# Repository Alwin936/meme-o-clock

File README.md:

This is the Meme-O-Clock PCB.

I built it with the help of a Youtube tutorial, ChatGPT, and KiCAD.

This is my first ever time designing a PCB.

I chose an Arduino Nano ESP 32 as my microcontroller due to the familiar ecosystem and WiFi capabilities.

The arduino will instruct a speaker and display to work as an alarm clock, with custom sounds and objects displayed to wake you up in a personal way.

Light sensor automatically adjusts display brightness based on the room.

Motion sensor will turn on display when motion detected.

MAX98357A amplifier for 5W, 8Ohm Speaker.

The whole project should cost under $30.

## Bill of Materials (BOM)

All prices are in USD and exclude shipping and tax. Prices are estimates or listed prices and may change.

### 1. PCB Components

| Component | Qty. | Part / Model | Unit Price | Supplier |
|---|---:|---|---:|---|
| Arduino Nano ESP32 | 1 | Arduino Nano ESP32 | $19.30 | [Arduino](https://store-usa.arduino.cc/products/nano-esp32) |
| USB-C receptacle | 1 | GCT USB4105-GF-A | $0.80 | [DigiKey](https://www.digikey.com/en/products/detail/gct/USB4105-GF-A/11198441) |
| JST EH 4-pin connector | 1 | S4B-EH | $0.116 | [GAM-GEC](https://gam-gec.com/product/s4b-eh/) |
| JST EH 2-pin connector | 1 | S2B-EH | $0.14 | [GAM-GEC](https://gam-gec.com/product/s2b-eh/) |
| JST EH 3-pin connector | 1 | S3B-EH | $0.17 | [GAM-GEC](https://gam-gec.com/product/s3b-eh/) |
| 10 kΩ resistor, 0603 | 4 | Stackpole RMCF0603FG10K0 | $0.10 | [DigiKey](https://www.digikey.com/en/products/detail/stackpole-electronics-inc/RMCF0603FG10K0/1761236) |
| 5.1 kΩ resistor, 0603 | 2 | Stackpole RNCF0603DTE5K10 | $0.10 | [DigiKey](https://www.digikey.com/en/products/detail/stackpole-electronics-inc/RNCF0603DTE5K10/6264054) |
| 634 kΩ resistor, 0603 | 1 | Vishay CRCW0603634KFKEA | $0.10 | [DigiKey](https://www.digikey.com/en/products/detail/vishay-dale/CRCW0603634KFKEA/1180130) |
| 6 × 6 mm tactile pushbutton, THT | 4 | Schurter 1301.9317 | $0.373 | [Newark](https://www.newark.com/) |
| I²S audio amplifier | 1 | MAX98357AETE+T | $4.08 | [DigiKey](https://www.digikey.com/en/products/detail/analog-devices-inc-maxim-integrated/MAX98357AETE-T/4936122) |
| Ambient light sensor | 1 | APDS-9306 | TBD | [Broadcom Datasheet](https://docs.broadcom.com/docs/AV02-4755EN) |
| Ceramic capacitor | 5 | 100 nF, 0603 | $0.05 | [TME](https://www.tme.com/us/en-us/details/c0603c104k4rac7081/mlcc-smd-capacitors/kemet/) |
| Ceramic capacitor | 1 | 1 µF, 0603 | $0.13 | [Mouser](https://www.mouser.com/en/c/passive-components/capacitors/ceramic-capacitors/mlccs-multilayer-ceramic-capacitors/multilayer-ceramic-capacitors-mlcc-smd-smt/?capacitance=1+uF&case+code+-+in=0603&dielectric=X7R&termination=Standard&voltage+rating+dc=10+VDC) |
| Ceramic capacitor | 1 | 10 µF, 0603 | $0.06 | [Mylsco](https://spartce.com/products/c1608x5r1a106m080ac-1) |

### 2. External Components

| Component | Qty. Needed | Product | Pack Price | Effective Unit Price | Supplier |
|---|---:|---|---:|---:|---|
| Speaker, 28 mm, 8 Ω, 2 W | 1 | 6-piece pack | TBD | TBD | [Amazon](https://www.amazon.com/dp/B09YGDQV3Z) |
| OLED display, 0.96 in, 128 × 64, SSD1306, I²C | 1 | ELEGOO 3-piece pack | $9.99 | $3.33 | [Amazon](https://www.amazon.com/dp/B0D2RMQQHR) |

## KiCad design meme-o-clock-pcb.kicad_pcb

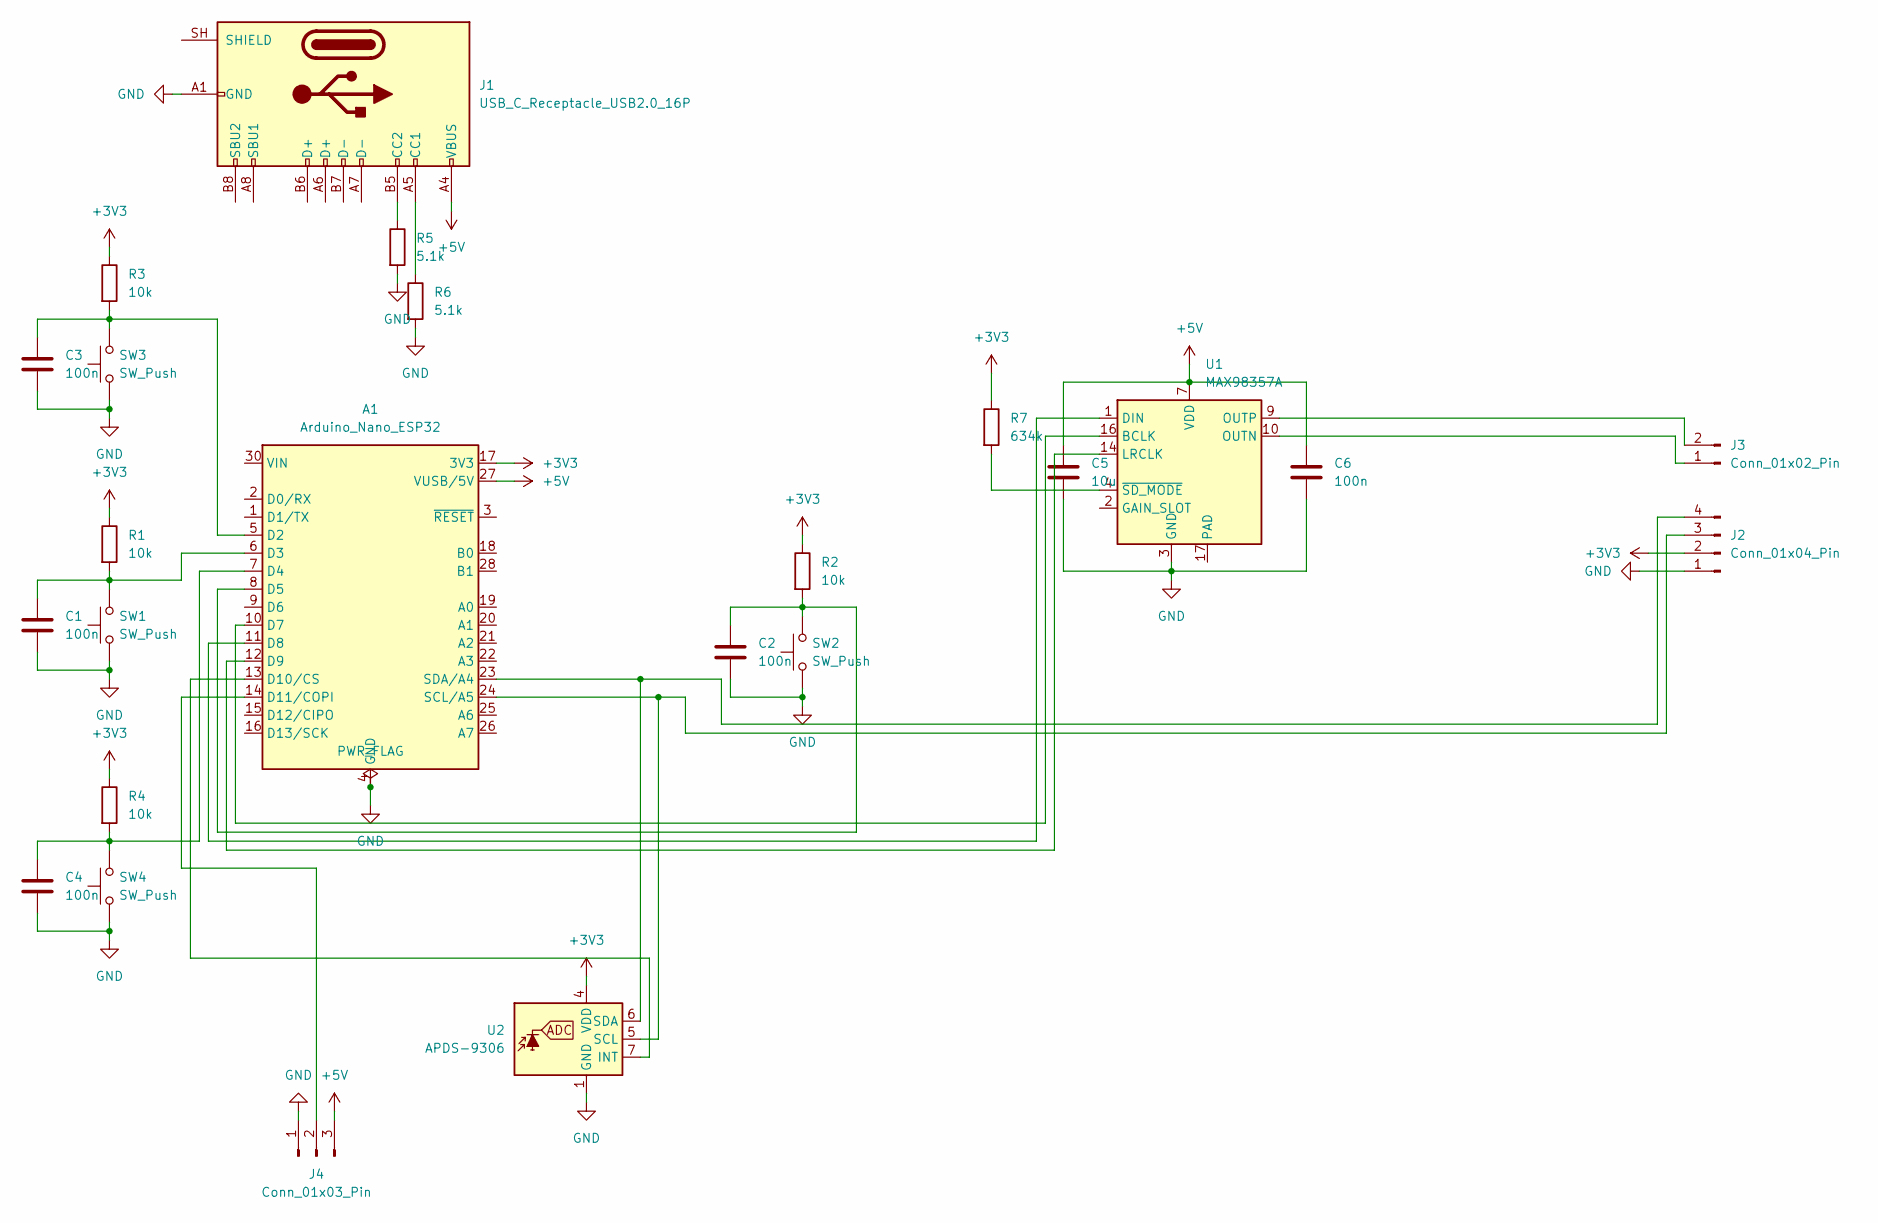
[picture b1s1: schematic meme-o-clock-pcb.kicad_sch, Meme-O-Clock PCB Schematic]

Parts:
A1: Arduino_Nano_ESP32; Arduino_Nano
C1, C2, C3, C4, C6: 100n; C_0603_1608Metric
C5: 10u; C_0805_2012Metric
J1: USB_C_Receptacle_USB2.0_16P; USB_C_Receptacle_GCT_USB4105-xx-A_16P_TopMnt_Horizontal
J2: Conn_01x04_Pin; PinHeader_1x04_P2.54mm_Vertical_SMD_Pin1Left
J3: Conn_01x02_Pin; JST_PH_B2B-PH-K_1x02_P2.00mm_Vertical
J4: Conn_01x03_Pin; PinHeader_1x03_P2.54mm_Vertical
R1, R2, R3, R4: 10k; R_0603_1608Metric
R5, R6: 5.1k; R_0603_1608Metric
R7: 634k; R_0603_1608Metric
SW1, SW2, SW3, SW4: SW_Push; SW_PUSH_6mm
U1: MAX98357A; TQFN-16-1EP_3x3mm_P0.5mm_EP1.23x1.23mm
U2: APDS-9306; Broadcom_LGA-8_2x2mm_P0.53mm

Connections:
+3V3: A1.17 (3V3), J2.2, R1.1, R2.1, R3.1, R4.1, R7.1, U2.4 (VDD)
+5V: A1.27 (VUSB/5V), C5.1, C6.1, J1.A4 (VBUS), J1.A9 (VBUS), J1.B4 (VBUS), J1.B9 (VBUS), J4.3, U1.7 (VDD), U1.8 (VDD)
GND: A1.4 (GND), A1.29 (GND), C1.2, C2.2, C3.2, C4.2, C5.2, C6.2, J1.A1 (GND), J1.A12 (GND), J1.B1 (GND), J1.B12 (GND), J2.1, J4.1, R5.2, R6.2, SW1.1, SW2.1, SW3.1, SW4.1, U1.3 (GND), U1.11 (GND), U1.15 (GND), U2.1 (GND)
unnamed: A1.5 (D2), C3.1, R3.2, SW3.2
unnamed: A1.6 (D3), C1.1, R1.2, SW1.2
unnamed: A1.7 (D4), C4.1, R4.2, SW4.2
unnamed: A1.8 (D5), C2.1, R2.2, SW2.2
unnamed: A1.10 (D7), U1.16 (BCLK)
unnamed: A1.11 (D8), U1.1 (DIN)
unnamed: A1.12 (D9), U1.14 (LRCLK)
unnamed: A1.13 (D10/CS), U2.7 (INT)
unnamed: A1.14 (D11/COPI), J4.2
unnamed: A1.24 (SCL/A5), J2.3, U2.5 (SCL)
unnamed: A1.23 (SDA/A4), J2.4, U2.6 (SDA)
unnamed: J1.A5 (CC1), R6.1
unnamed: J1.B5 (CC2), R5.1
unnamed: J3.1, U1.10 (OUTN)
unnamed: J3.2, U1.9 (OUTP)
unnamed: R7.2, U1.4 (~SD_MODE)

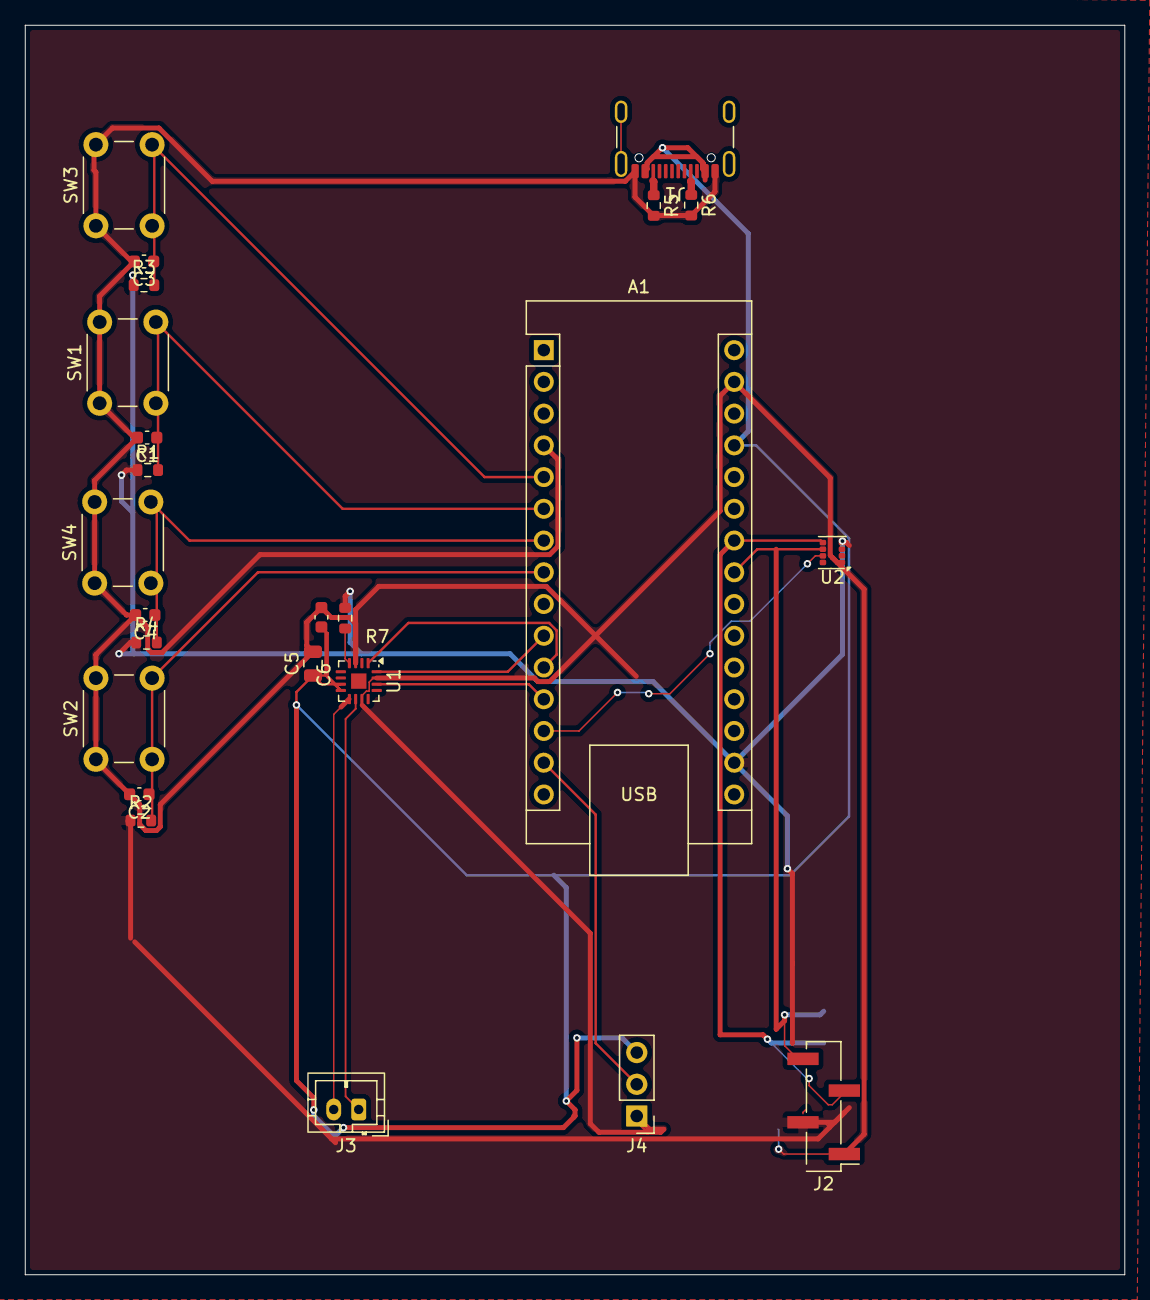
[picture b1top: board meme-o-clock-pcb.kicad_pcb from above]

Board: 4 copper layers, 88.0 x 100.0 mm, 24 parts (0 on the bottom side), 19 nets.

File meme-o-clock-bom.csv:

"Reference","Qty","Value","DNP","Exclude from BOM","Exclude from Board","Exclude from Simulation","Exclude from Position Files","Footprint","Datasheet"
"A1","1","Arduino_Nano_ESP32","","","","","${EXCLUDE_FROM_POS_FILES}","Module:Arduino_Nano","https://docs.arduino.cc/resources/datasheets/ABX00083-datasheet.pdf"
"C1,C2,C3,C4,C6","5","100n","","","","","${EXCLUDE_FROM_POS_FILES}","Capacitor_SMD:C_0603_1608Metric",""
"C5","1","10u","","","","","${EXCLUDE_FROM_POS_FILES}","Capacitor_SMD:C_0805_2012Metric",""
"J1","1","USB_C_Receptacle_USB2.0_16P","","","","","${EXCLUDE_FROM_POS_FILES}","Connector_USB:USB_C_Receptacle_GCT_USB4105-xx-A_16P_TopMnt_Horizontal","https://www.usb.org/sites/default/files/documents/usb_type-c.zip"
"J2","1","Conn_01x04_Pin","","","","","${EXCLUDE_FROM_POS_FILES}","Connector_JST:JST_EH_S4B-EH_1x04_P2.50mm_Horizontal",""
"J3","1","Conn_01x02_Pin","","","","","${EXCLUDE_FROM_POS_FILES}","Connector_JST:JST_EH_S2B-EH_1x02_P2.50mm_Horizontal",""
"J4","1","Conn_01x03_Pin","","","","","${EXCLUDE_FROM_POS_FILES}","Connector_JST:JST_EH_S3B-EH_1x03_P2.50mm_Horizontal",""
"R1,R2,R3,R4","4","10k","","","","","${EXCLUDE_FROM_POS_FILES}","Resistor_SMD:R_0603_1608Metric",""
"R5,R6","2","5.1k","","","","","${EXCLUDE_FROM_POS_FILES}","Resistor_SMD:R_0603_1608Metric",""
"R7","1","634k","","","","","${EXCLUDE_FROM_POS_FILES}","Resistor_SMD:R_0603_1608Metric",""
"SW1,SW2,SW3,SW4","4","SW_Push","","","","","${EXCLUDE_FROM_POS_FILES}","Button_Switch_THT:SW_PUSH_6mm",""
"U1","1","MAX98357A","","","","","${EXCLUDE_FROM_POS_FILES}","Package_DFN_QFN:TQFN-16-1EP_3x3mm_P0.5mm_EP1.23x1.23mm","https://www.analog.com/media/en/technical-documentation/data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"
"U2","1","APDS-9306","","","","","${EXCLUDE_FROM_POS_FILES}","OptoDevice:Broadcom_LGA-8_2x2mm_P0.53mm","https://docs.broadcom.com/docs/AV02-4755EN"
